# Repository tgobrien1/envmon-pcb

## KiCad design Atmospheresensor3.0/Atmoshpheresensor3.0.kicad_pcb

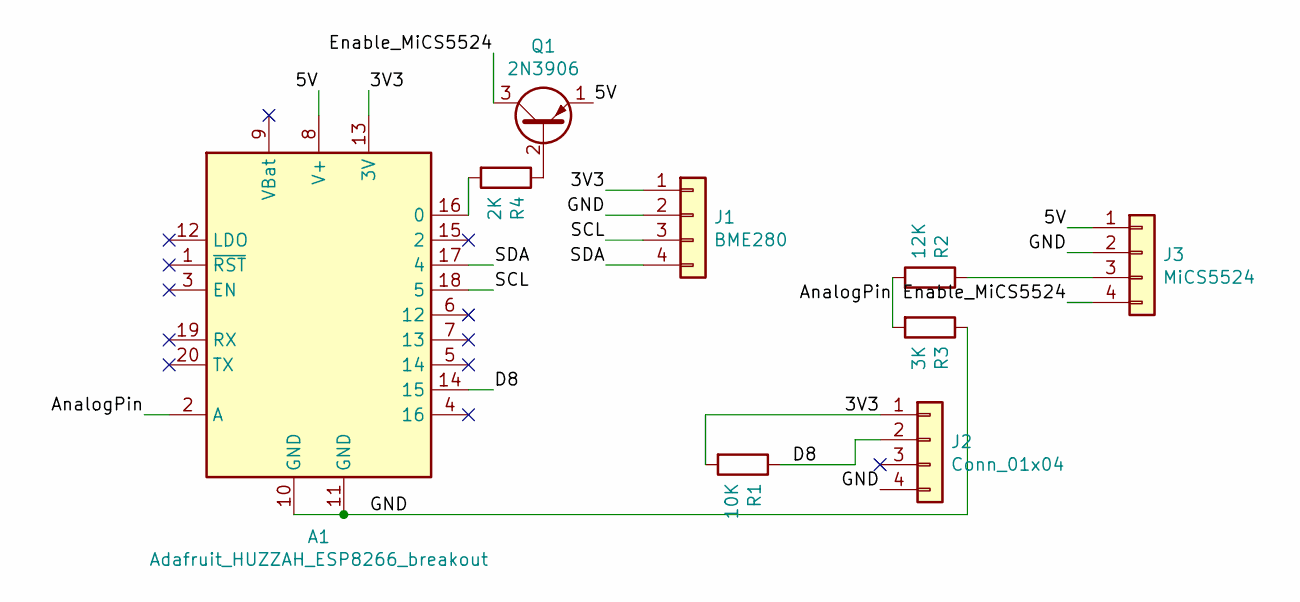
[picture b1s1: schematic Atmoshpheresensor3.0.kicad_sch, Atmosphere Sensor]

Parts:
A1: Adafruit_HUZZAH_ESP8266_breakout; XCVR_ADA2471
J1: BME280; PinHeader_1x04_P2.54mm_Vertical
J2: Conn_01x04; PinHeader_1x04_P2.54mm_Vertical
J3: MiCS5524; PinHeader_1x04_P2.54mm_Vertical
Q1: 2N3906; TO-92_Inline
R1: 10K; R_Axial_DIN0207_L6.3mm_D2.5mm_P7.62mm_Horizontal
R2: 12K; R_Axial_DIN0207_L6.3mm_D2.5mm_P7.62mm_Horizontal
R3: 3K; R_Axial_DIN0207_L6.3mm_D2.5mm_P7.62mm_Horizontal
R4: 2K; R_Axial_DIN0207_L6.3mm_D2.5mm_P7.62mm_Horizontal

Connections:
/3V3: A1.13 (3V), J1.1, J2.1, R1.2
/5V: A1.8 (V+), J3.1, Q1.1 (E)
/AnalogPin: A1.2 (A), R2.2, R3.2
/D8: A1.14 (15), J2.2, R1.1
/Enable_MiCS5524: J3.4, Q1.3 (C)
/GND: A1.10 (GND), A1.11 (GND), J1.2, J2.4, J3.2, R3.1
/SCL: A1.18 (5), J1.3
/SDA: A1.17 (4), J1.4
unnamed: A1.16 (0), R4.2
unnamed: J3.3, R2.1
unnamed: Q1.2 (B), R4.1

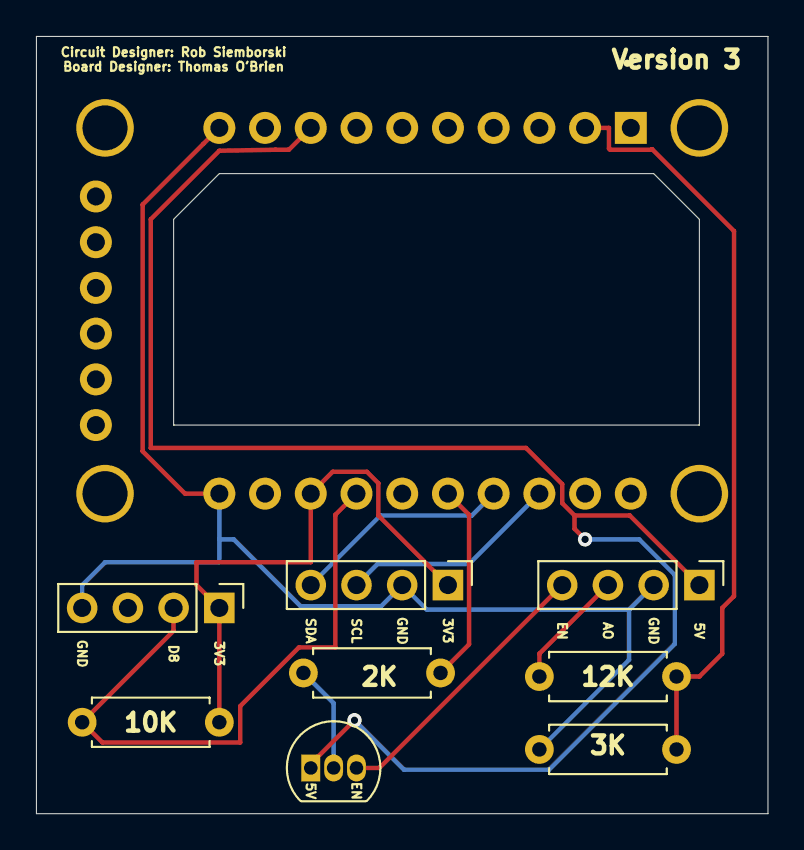
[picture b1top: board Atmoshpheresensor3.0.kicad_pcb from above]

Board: 2 copper layers, 40.6 x 43.2 mm, 9 parts (0 on the bottom side), 11 nets.

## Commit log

2022-02-05 Initial Import
    This is verion 3 of the sensor pcb for the environmental monitoring project created by @robsiemb
2022-02-05 Update Title Block
    Add the rev & title
